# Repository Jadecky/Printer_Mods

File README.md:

# Kyle🇬🇧’s Printer Chaos, Mods & Configs 🛠️
Home to my various mods & QOL Updates for printers I've built, along with config backups.

---

## 🐝 My Printers
|**Name**|**Printer**|**Voron Serial**|**PFA Serial**|**Status**|
|-----|-----|-----|-----|-----|
| **Bee.Zero** | [Voron V0](https://vorondesign.com/voron0.2) | V0.1848 | N/A | On sabbatical (lazy bee vibes) |
| **Bee.Two** | [Micron R1](https://github.com/PrintersForAnts/Micron) | V2.6033 | M.055 | Current Workhorse 🐝 |
| **Bee.Three** | [StealthFork](https://github.com/PrintersForAnts/StealthFork) | SF.xxx | VT.xxxx | Work in Progress |
| **Bee.Four** | FireAnt | V2.xxxx | TBC | In Design Stage 🔥 |
| **Rex 🦖** | [Micron R1 - LDO Beta](https://github.com/PrintersForAnts/Micron) | V2.xxxx | M.202 | Tuning |

---

## 🛠️ Mods & Parts

### - [Micron Things](https://github.com/Jadecky/Printer-Mods/tree/main/Micron%2B)

### - [Voron V0 Things](https://github.com/Jadecky/Printer_Mods/tree/main/V0)

### - [Misc Items](https://github.com/Jadecky/Printer_Mods/tree/main/Misc%20Items)

---

## 🐜 Printers for Ants Items

### - [StealthFork](https://github.com/PrintersForAnts/StealthFork)
The one where Micron & Salad Fork had a baby...

### - [Colony Clacker](https://github.com/PrintersForAnts/ColonyClacker)
Tiny printer? Tiny door? Needs a satisfying clack

---

## 💾 Config Backups

### - [**Micron M.055**](https://github.com/Jadecky/Micron_Configs)

### - **Voron V0.1848** - Still need to setup auto commit 

### - **Micron M.202** - Still need to setup auto commit 

---

Most of these mods are also listed on my [Printables page](https://www.printables.com/@Jadecky3D/models) — if you like what you see, toss me a like or post a make to help me earn that gucci free spool 🧵 and keep the upgrades coming.

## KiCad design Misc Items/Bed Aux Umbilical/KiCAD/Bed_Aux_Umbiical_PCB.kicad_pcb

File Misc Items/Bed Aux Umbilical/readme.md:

### Bed Aux Umbilical ###

Originally designed for Micron R1, with a corresponding mount that replaces the Wago mount on the filter. 

These are included in the LDO Micron R1 Kit.

More information to follow.

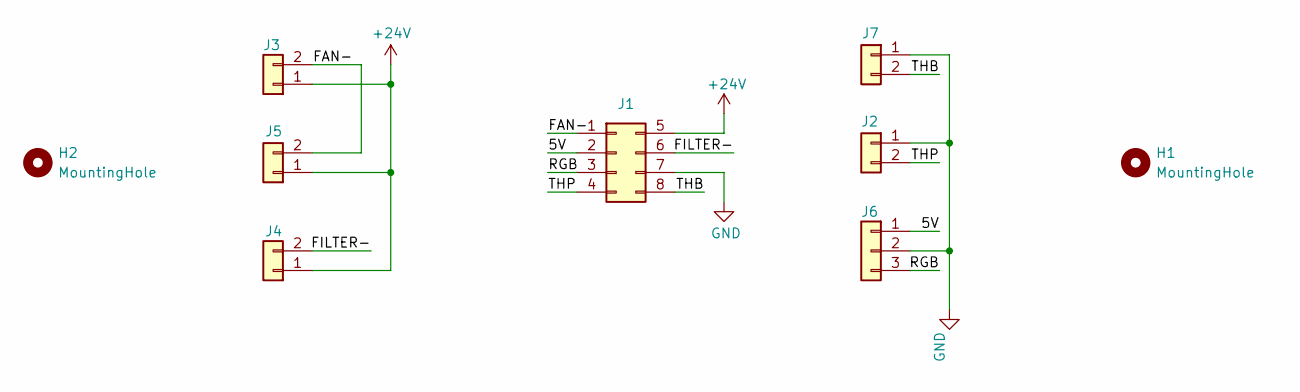
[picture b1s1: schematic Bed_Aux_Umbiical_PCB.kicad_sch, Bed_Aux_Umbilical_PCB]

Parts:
H1, H2: MountingHole; MountingHoleBare_M3
J1: Conn_02x04_Odd_Even; Molex_Micro-Fit_3.0_43045-0800_2x04_P3.00mm_Horizontal
J2, J3, J4, J5, J7: JST-XHP-02; JST_XH_S2B-XH-A-1_1x02_P2.50mm_Horizontal
J6: JST-XHP-02; JST_XH_S3B-XH-A-1_1x03_P2.50mm_Horizontal

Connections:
+24V: J1.5, J3.1, J4.1, J5.1
/5V: J1.2, J6.1
/FAN-: J1.1, J3.2, J5.2
/FILTER-: J1.6, J4.2
/RGB: J1.3, J6.3
/THB: J1.8, J7.2
/THP: J1.4, J2.2
GND: J1.7, J2.1, J6.2, J7.1

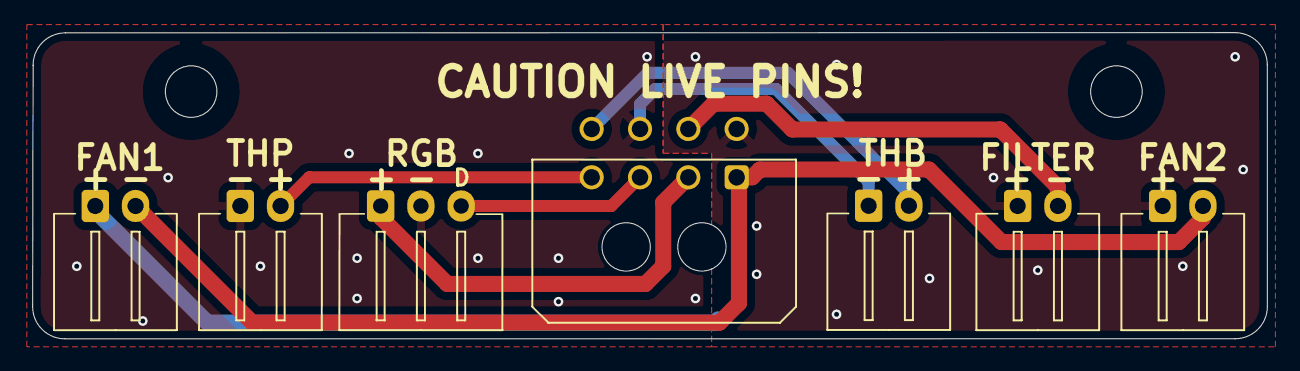
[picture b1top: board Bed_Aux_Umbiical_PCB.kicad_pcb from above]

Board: 2 copper layers, 76.6 x 19.0 mm, 9 parts (0 on the bottom side), 8 nets.

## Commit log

2023-08-23 Initial set up
2023-08-23 Create LICENSE
2023-08-28 Add Z Belt Clamp & KGLM Z Joint
2023-08-28 Update links to correct ones
2023-08-29 Correct logo orientation
2023-09-10 Tidy up readme.md
2023-09-10 Add MDC
    First iteration of MDC (Magnetic Door Corners).
2023-09-10 Add heatsets to BOM
2023-09-10 Add correct QTY for heatsets
2023-12-18 added Matchstick Mounts
2024-08-17 Upload WAGO 221-415 Mounts
2024-08-17 Upload Micron Electronics Bay WAGO 221-415 Mounts
2024-08-23 Add ERCF 1515 Mounts
2024-08-23 Update ERCF 1515 Mount Readme
2024-10-31 Added F623 Bearing Repacker and updated readme's
2024-10-31 Add Misc Items to README.md
2024-10-31 add images to readme.md
2024-10-31 what is hanfdling?
    removed typo.
2024-11-20 Add Micron Purge Bucket
2024-11-20 Fixed table in readme
2025-02-17 Add V0 Mods
    Add V0 Folder
    Add V0 Rear DIN Rail Mounts
    Add V0 Lower DIN Rail Mounts
    Add V0 UHP Mount
2025-02-17 Add V0 Things link.md
2025-06-05 Upload Macros
    Added `nozzle_brush.cfg` & `nozzle_poop.cfg`
2025-06-16 Adding stock Micron base
2025-06-29 Remove .DS_Store files
2025-06-29 Rep Spring Clean
    - Removed all .DS_store and macOS files
    - Cleaned Up Folders
    - Added Stealth Fan Grills
    - Added Single Piece Skirt Accent
    - Cleaned up all readme.md
    - Added Printer Information table
2025-06-29 Fix broken links
2025-07-15 Upload Dual Colour Spool Holder
2025-07-15 update broken image links
2025-07-15 Upload Display Bezel Border Accent
2025-07-20 Upload really useful tool
2025-08-09 Remove .DS_Store files and add to .gitignore
2025-08-09 Remove tracked .DS_Store files
2025-10-04 Upload AntHead NH36 Mount
2025-10-28 Upload Micron NEMA17
2025-11-23 Added Brush on Left Variant, and LDO Kit specific parts
2025-11-23 Uploaded Bed Aux Umbilical
